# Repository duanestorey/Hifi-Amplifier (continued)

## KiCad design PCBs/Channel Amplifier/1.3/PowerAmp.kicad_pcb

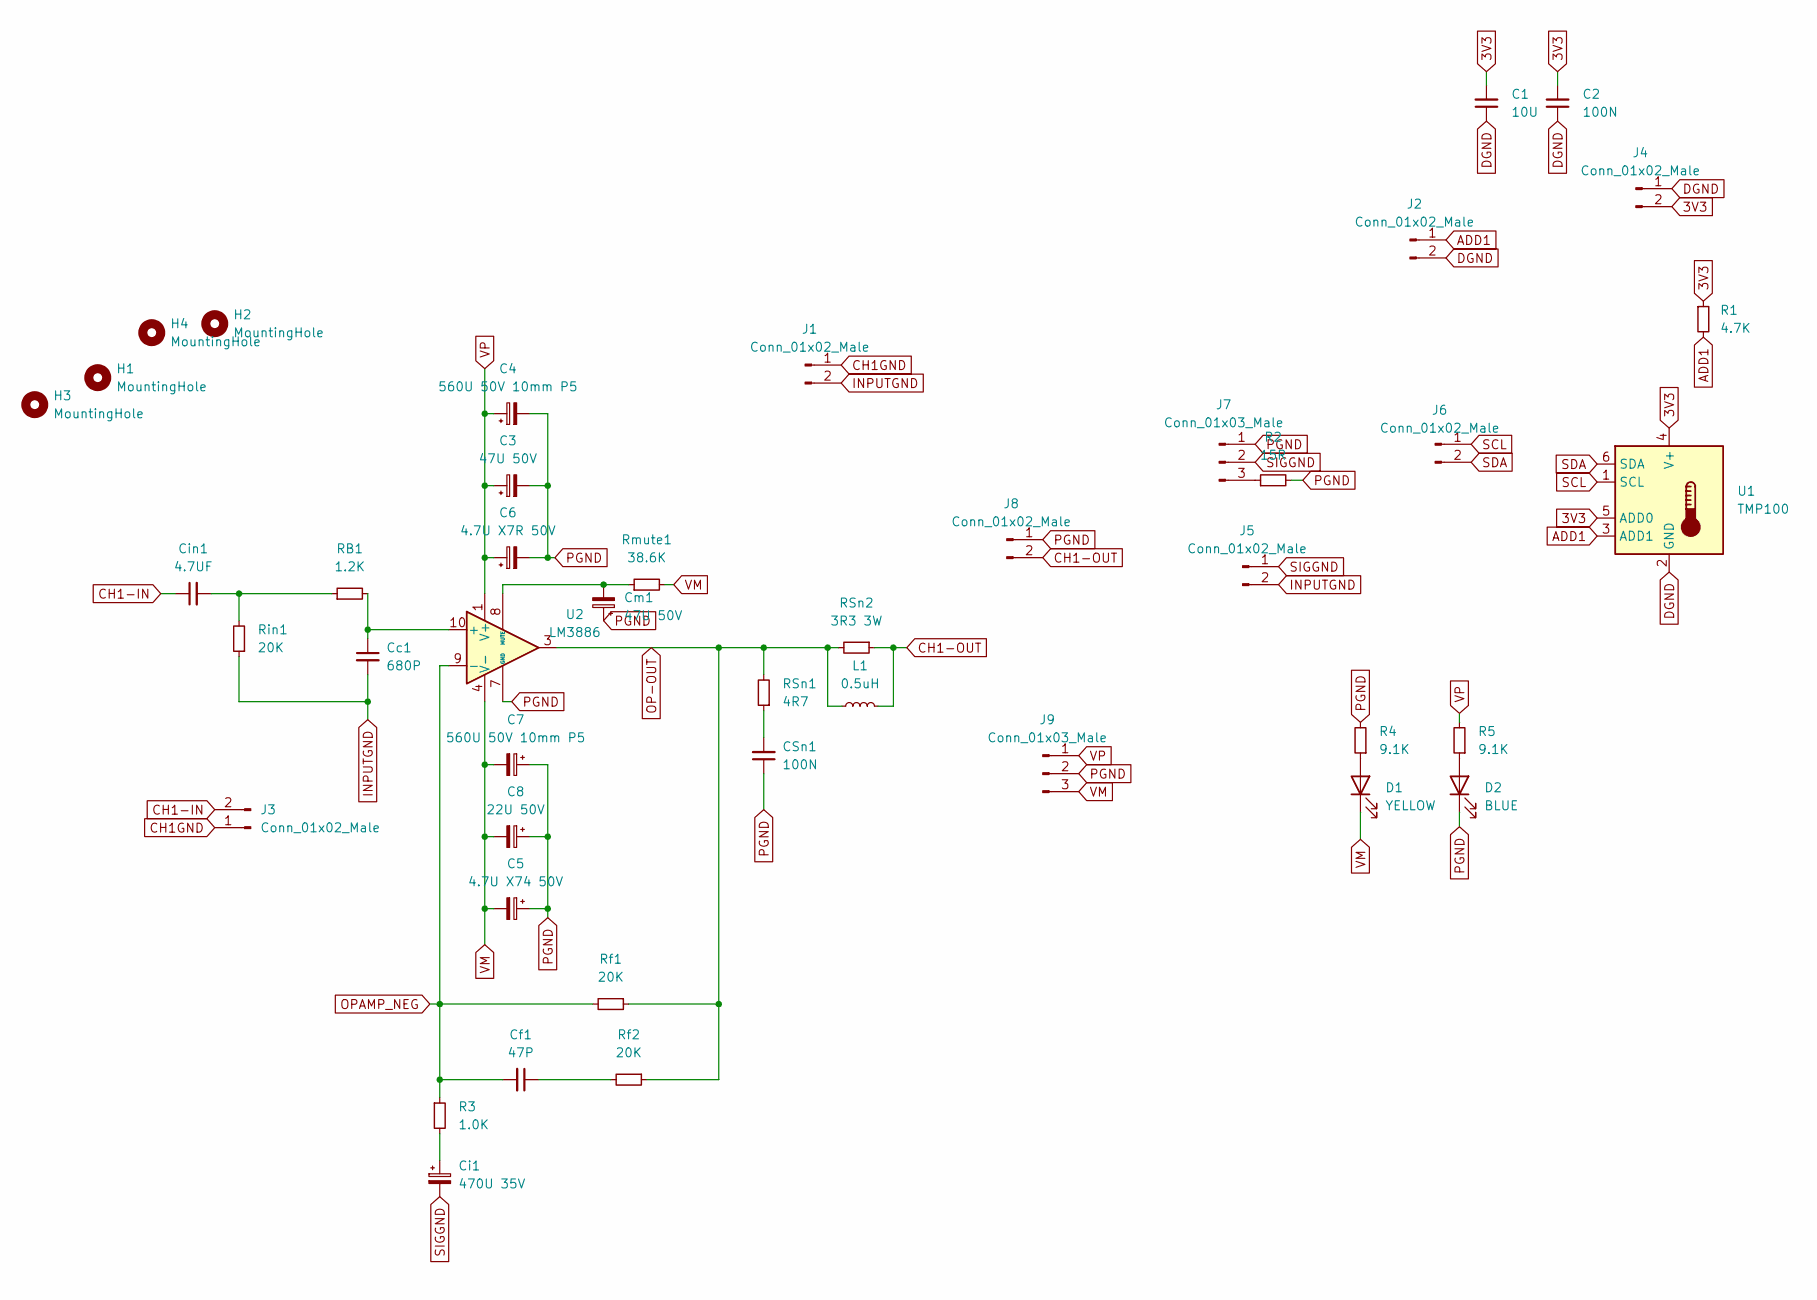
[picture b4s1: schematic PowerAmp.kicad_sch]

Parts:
C1: 10U; R_1206_3216Metric_Pad1.30x1.75mm_HandSolder
C2: 100N; R_0805_2012Metric_Pad1.20x1.40mm_HandSolder
C3: 47U 50V; CP_Radial_D6.3mm_P2.50mm
C4, C7: 560U 50V 10mm P5; CP_Radial_D12.5mm_P5.00mm
C5: 4.7U X74 50V; C_Disc_D6.0mm_W4.4mm_P5.00mm
C6: 4.7U X7R 50V; C_Disc_D6.0mm_W4.4mm_P5.00mm
C8: 22U 50V; CP_Radial_D6.3mm_P2.50mm
CSn1: 100N; C_Rect_L10.3mm_W4.5mm_P7.50mm_MKS4
Cc1: 680P; C_Disc_D11.0mm_W5.0mm_P10.00mm
Cf1: 47P; C_Disc_D9.0mm_W5.0mm_P7.50mm
Ci1: 470U 35V; CP_Radial_D10.0mm_P5.00mm
Cin1: 4.7UF; CP_Radial_D5.0mm_P2.00mm
Cm1: 47U 50V; CP_Radial_D6.3mm_P2.50mm
D1: YELLOW; LED_0805_2012Metric_Pad1.15x1.40mm_HandSolder
D2: BLUE; LED_0805_2012Metric_Pad1.15x1.40mm_HandSolder
H1, H2, H3, H4: MountingHole; MountingHole_3mm
J1, J2, J5: Conn_01x02_Male; PinHeader_1x02_P2.54mm_Vertical
J3, J4, J6: Conn_01x02_Male; JST_PH_B2B-PH-K_1x02_P2.00mm_Vertical
J7: Conn_01x03_Male; PinHeader_1x03_P2.54mm_Vertical
J8: Conn_01x02_Male; JST_VH_B2P-VH_1x02_P3.96mm_Vertical
J9: Conn_01x03_Male; JST_VH_B3P-VH-B_1x03_P3.96mm_Vertical
L1: 0.5uH; L_Radial_D12.0mm_P10.00mm_Neosid_SD12_style1
R1: 4.7K; R_0603_1608Metric_Pad0.98x0.95mm_HandSolder
R2: 15R; R_1206_3216Metric_Pad1.30x1.75mm_HandSolder
R3: 1.0K; R_Axial_DIN0207_L6.3mm_D2.5mm_P10.16mm_Horizontal
R4, R5: 9.1K; R_0805_2012Metric_Pad1.20x1.40mm_HandSolder
RB1: 1.2K; R_Axial_DIN0207_L6.3mm_D2.5mm_P10.16mm_Horizontal
RSn1: 4R7; R_Axial_DIN0411_L9.9mm_D3.6mm_P12.70mm_Horizontal
RSn2: 3R3 3W; R_Axial_DIN0516_L15.5mm_D5.0mm_P20.32mm_Horizontal
Rf1, Rf2: 20K; R_Axial_DIN0207_L6.3mm_D2.5mm_P10.16mm_Horizontal
Rin1: 20K; R_Axial_DIN0207_L6.3mm_D2.5mm_P10.16mm_Horizontal
Rmute1: 38.6K; R_Axial_DIN0207_L6.3mm_D2.5mm_P10.16mm_Horizontal
U1: TMP100; SOT-23-6
U2: LM3886; TO-220-11_P3.4x5.08mm_StaggerOdd_Lead4.85mm_Vertical

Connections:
3V3: C1.2, C2.2, J4.2, R1.1, U1.4 (V+), U1.5 (ADD0)
ADD1: J2.1, R1.2, U1.3 (ADD1)
CH1-IN: Cin1.1, J3.2
CH1-OUT: J8.2, L1.2, RSn2.1
CH1GND: J1.1, J3.1
DGND: C1.1, C2.1, J2.2, J4.1, U1.2 (GND)
INPUTGND: Cc1.2, J1.2, J5.2, Rin1.1
unnamed: CSn1.2, RSn1.1
unnamed: Cf1.1, Rf2.2
unnamed: Ci1.1, R3.2
unnamed: Cin1.2, RB1.1, Rin1.2
unnamed: D1.2 (A), R4.1
unnamed: D2.2 (A), R5.1
unnamed: J7.3, R2.1
unnamed: Cc1.1, RB1.2, U2.10 (+)
unnamed: Cm1.2, Rmute1.1, U2.8 (MUTE)
OP-OUT: L1.1, RSn1.2, RSn2.2, Rf1.1, Rf2.1, U2.3
OPAMP_NEG: Cf1.2, R3.1, Rf1.2, U2.9 (-)
PGND: C3.2, C4.2, C5.1, C6.2, C7.1, C8.1, CSn1.1, Cm1.1, D2.1 (K), J7.1, J8.1, J9.2, R2.2, R4.2, U2.7 (GND)
SCL: J6.1, U1.1 (SCL)
SDA: J6.2, U1.6 (SDA)
SIGGND: Ci1.2, J5.1, J7.2
VM: C5.2, C7.2, C8.2, D1.1 (K), J9.3, Rmute1.2, U2.4 (V-)
VP: C3.1, C4.1, C6.1, J9.1, R5.2, U2.1 (V+), U2.5 (V+)

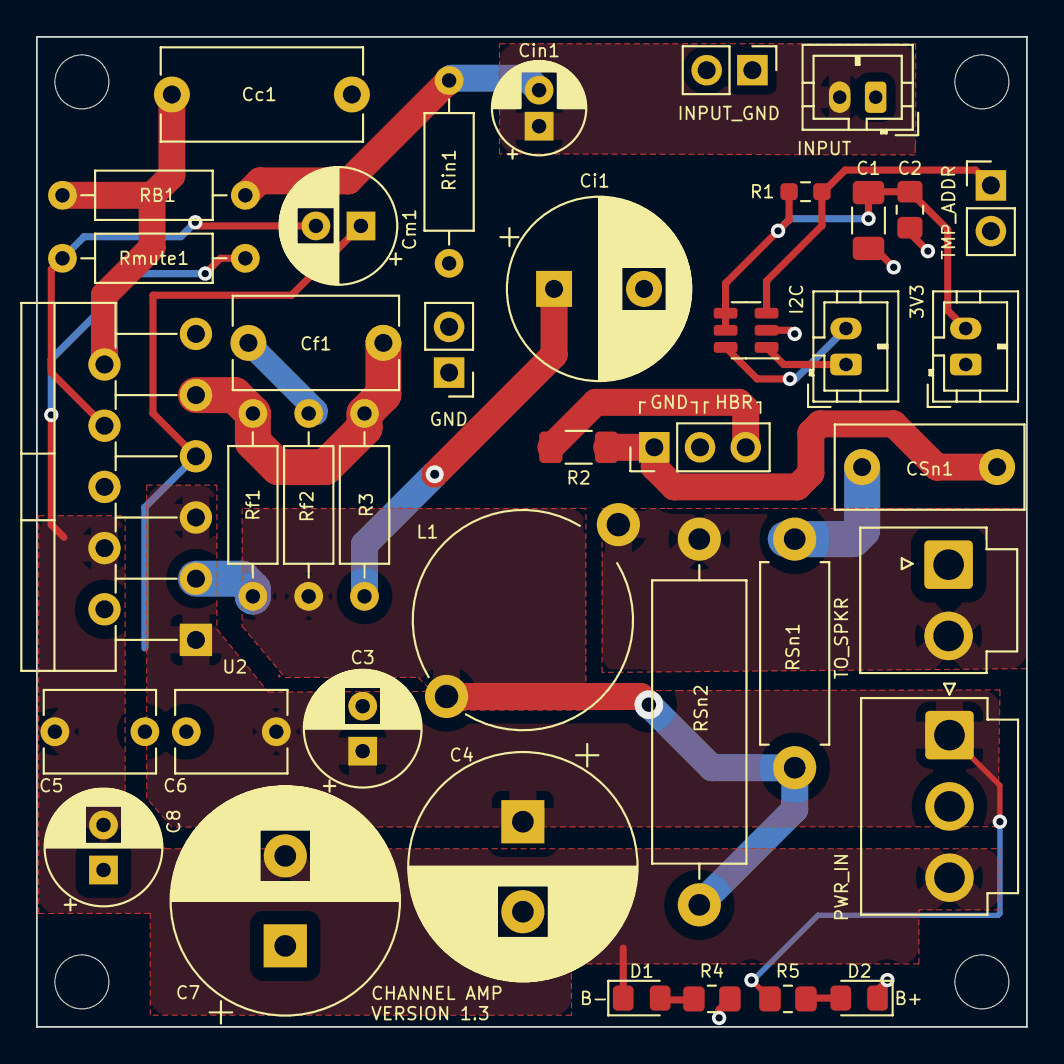
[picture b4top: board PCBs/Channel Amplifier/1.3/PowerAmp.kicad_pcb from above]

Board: 2 copper layers, 55.0 x 55.0 mm, 44 parts (0 on the bottom side), 24 nets.

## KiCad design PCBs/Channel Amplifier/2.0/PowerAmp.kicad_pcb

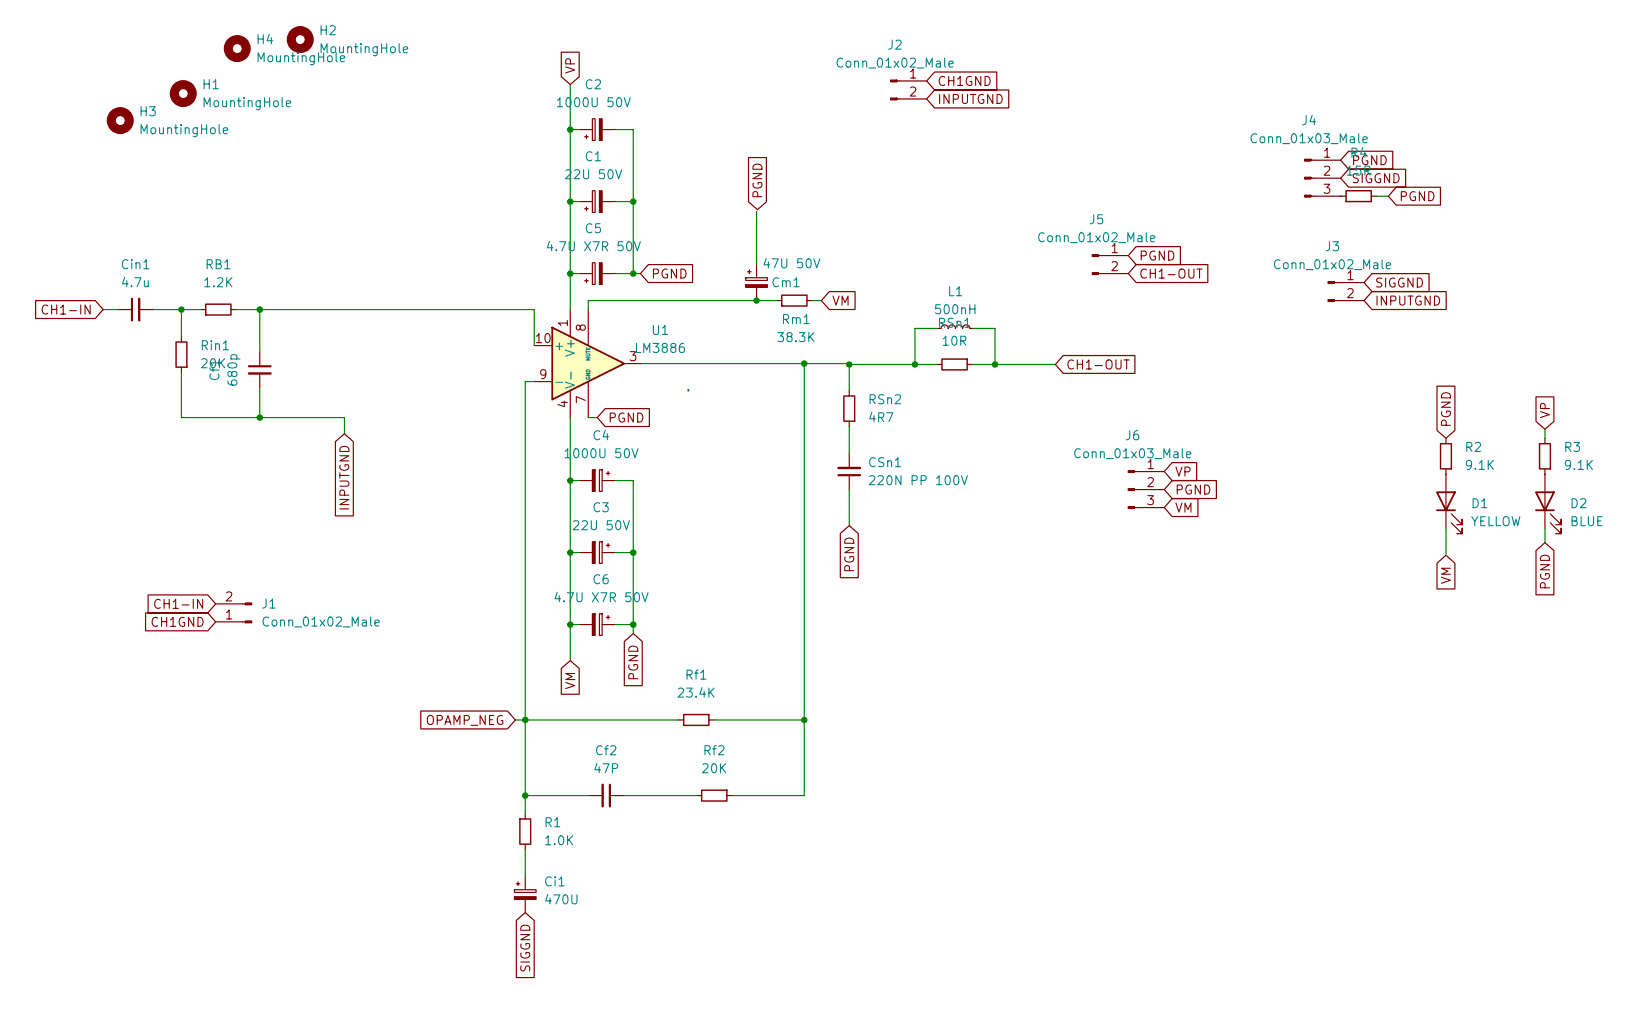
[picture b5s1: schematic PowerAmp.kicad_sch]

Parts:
C1, C3: 22U 50V; CP_Radial_D6.3mm_P2.50mm
C2, C4: 1000U 50V; CP_Radial_D12.5mm_P5.00mm
C5, C6: 4.7U X7R 50V; C_1206_3216Metric_Pad1.33x1.80mm_HandSolder
CSn1: 220N PP 100V; C_Rect_L18.0mm_W7.0mm_P15.00mm_FKS3_FKP3
Cf1: 680p; C_1206_3216Metric_Pad1.33x1.80mm_HandSolder
Cf2: 47P; C_1206_3216Metric_Pad1.33x1.80mm_HandSolder
Ci1: 470U; CP_Radial_D12.5mm_P5.00mm
Cin1: 4.7u; 4.7uF Polypropylene Aliexpress
Cm1: 47U 50V; CP_Radial_D6.3mm_P2.50mm
D1: YELLOW; LED_0805_2012Metric_Pad1.15x1.40mm_HandSolder
D2: BLUE; LED_0805_2012Metric_Pad1.15x1.40mm_HandSolder
H1, H2, H3, H4: MountingHole; MountingHole_3mm
J1: Conn_01x02_Male; JST_PH_B2B-PH-K_1x02_P2.00mm_Vertical
J2, J3: Conn_01x02_Male; PinHeader_1x02_P2.54mm_Vertical
J4: Conn_01x03_Male; PinHeader_1x03_P2.54mm_Vertical
J5: Conn_01x02_Male; JST_VH_B2P-VH_1x02_P3.96mm_Vertical
J6: Conn_01x03_Male; JST_VH_B3P-VH-B_1x03_P3.96mm_Vertical
L1: 500nH; 500nH Inductor Aliexpress Air Gap
R1: 1.0K; R_1206_3216Metric_Pad1.30x1.75mm_HandSolder
R2, R3: 9.1K; R_0805_2012Metric_Pad1.20x1.40mm_HandSolder
R4: 15R; R_0805_2012Metric_Pad1.20x1.40mm_HandSolder
RB1: 1.2K; R_1206_3216Metric_Pad1.30x1.75mm_HandSolder
RSn1: 10R; R_4020_10251Metric_Pad1.65x5.30mm_HandSolder
RSn2: 4R7; R_Axial_DIN0411_L9.9mm_D3.6mm_P12.70mm_Horizontal
Rf1: 23.4K; R_1206_3216Metric_Pad1.30x1.75mm_HandSolder
Rf2: 20K; R_1206_3216Metric_Pad1.30x1.75mm_HandSolder
Rin1: 20K; R_1206_3216Metric_Pad1.30x1.75mm_HandSolder
Rm1: 38.3K; R_1206_3216Metric_Pad1.30x1.75mm_HandSolder
U1: LM3886; TO-220-11_P3.4x5.08mm_StaggerOdd_Lead4.85mm_Vertical

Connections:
CH1-IN: Cin1.1, J1.2
CH1-OUT: J5.2, L1.2, RSn1.1
CH1GND: J1.1, J2.1
INPUTGND: Cf1.2, J2.2, J3.2, Rin1.1
unnamed: CSn1.2, RSn2.1
unnamed: Cf2.1, Rf2.2
unnamed: Ci1.1, R1.2
unnamed: Cin1.2, RB1.1, Rin1.2
unnamed: D1.2 (A), R2.1
unnamed: D2.2 (A), R3.1
unnamed: J4.3, R4.1
unnamed: L1.1, RSn1.2, RSn2.2, Rf1.1, Rf2.1, U1.3
unnamed: Cf1.1, RB1.2, U1.10 (+)
unnamed: Cm1.2, Rm1.1, U1.8 (MUTE)
OPAMP_NEG: Cf2.2, R1.1, Rf1.2, U1.9 (-)
PGND: C1.2, C2.2, C3.1, C4.1, C5.2, C6.1, CSn1.1, D2.1 (K), J4.1, J5.1, J6.2, R2.2, R4.2, U1.7 (GND)
SIGGND: Ci1.2, J3.1, J4.2
VM: C3.2, C4.2, C6.2, D1.1 (K), J6.3, Rm1.2, U1.4 (V-)
VP: C1.1, C2.1, C5.1, J6.1, R3.2, U1.1 (V+), U1.5 (V+)

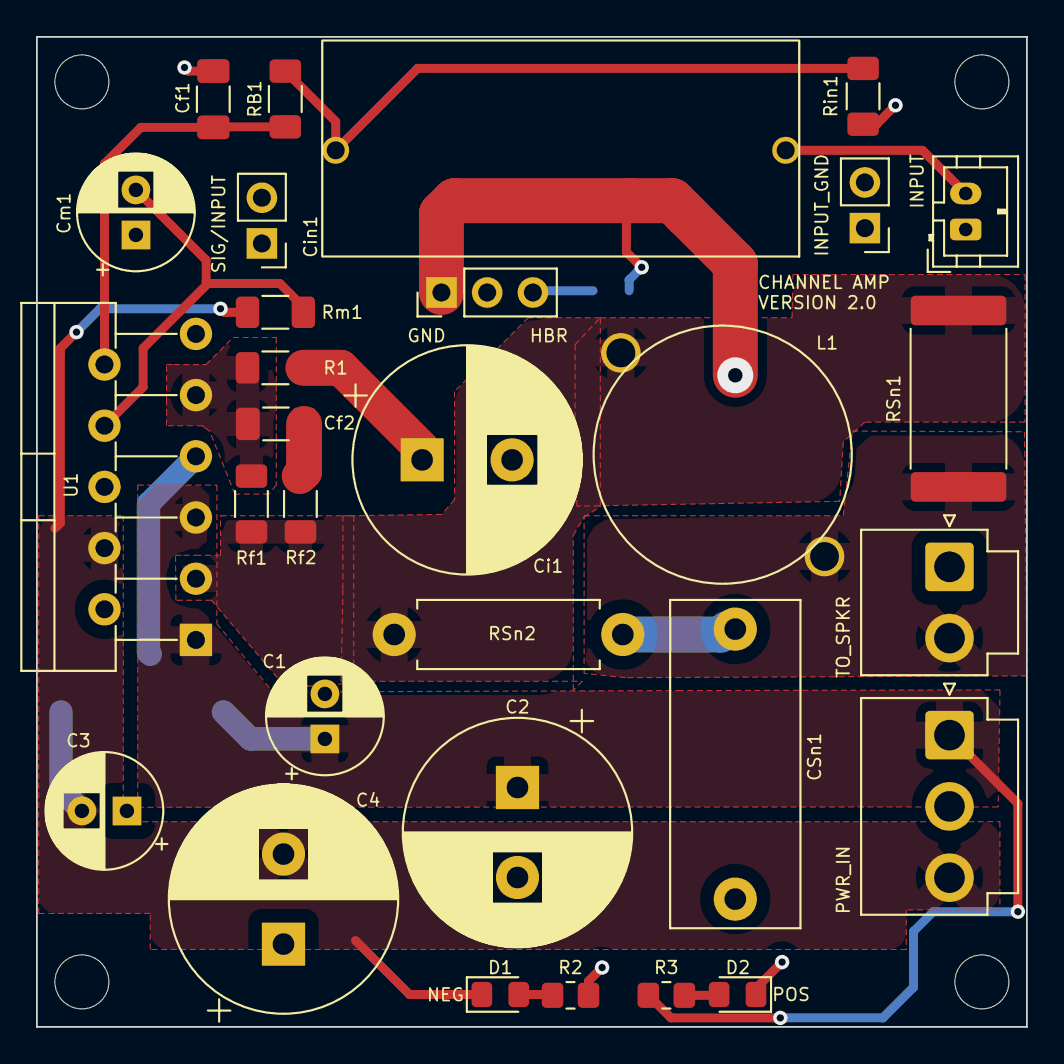
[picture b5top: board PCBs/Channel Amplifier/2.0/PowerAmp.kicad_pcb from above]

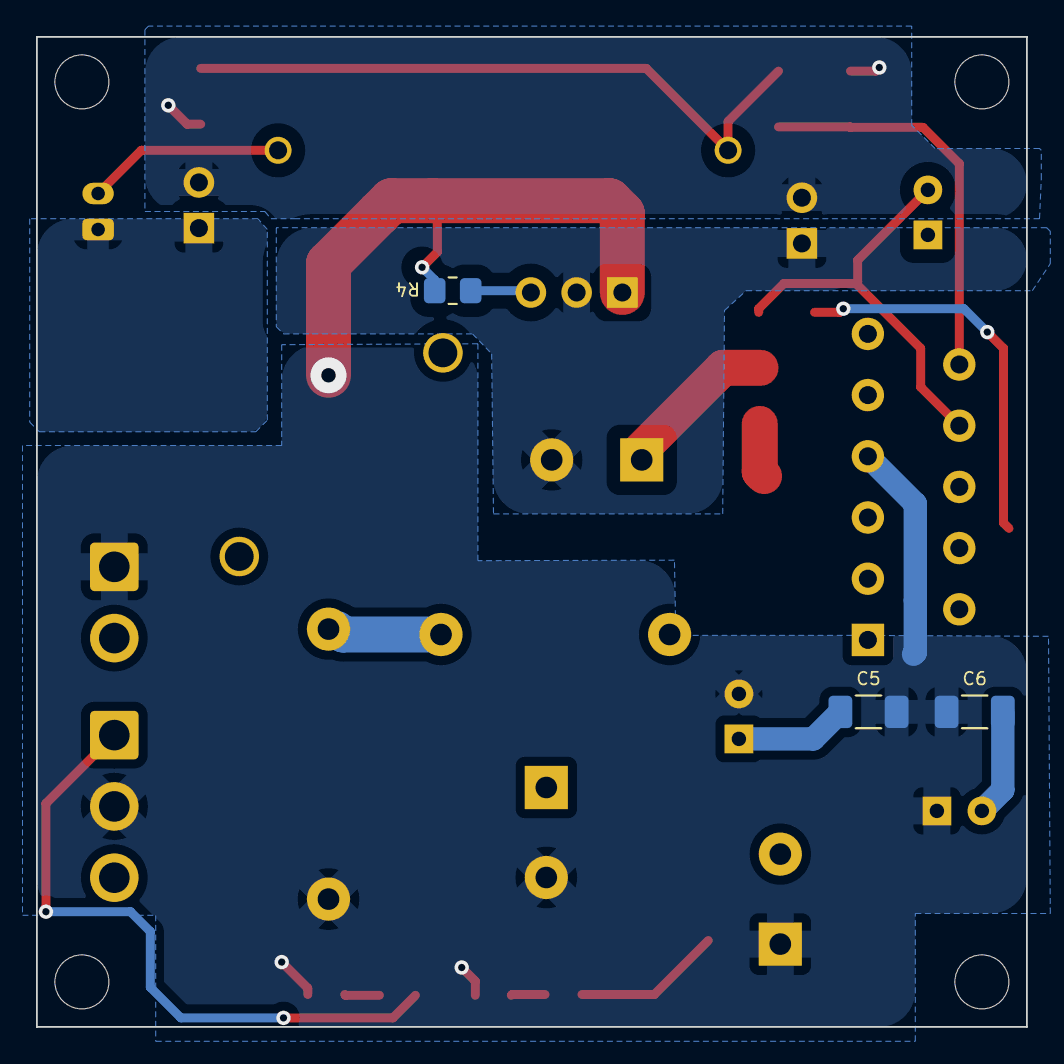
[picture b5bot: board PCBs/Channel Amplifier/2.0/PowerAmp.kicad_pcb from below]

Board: 2 copper layers, 55.0 x 55.0 mm, 37 parts (3 on the bottom side), 19 nets.

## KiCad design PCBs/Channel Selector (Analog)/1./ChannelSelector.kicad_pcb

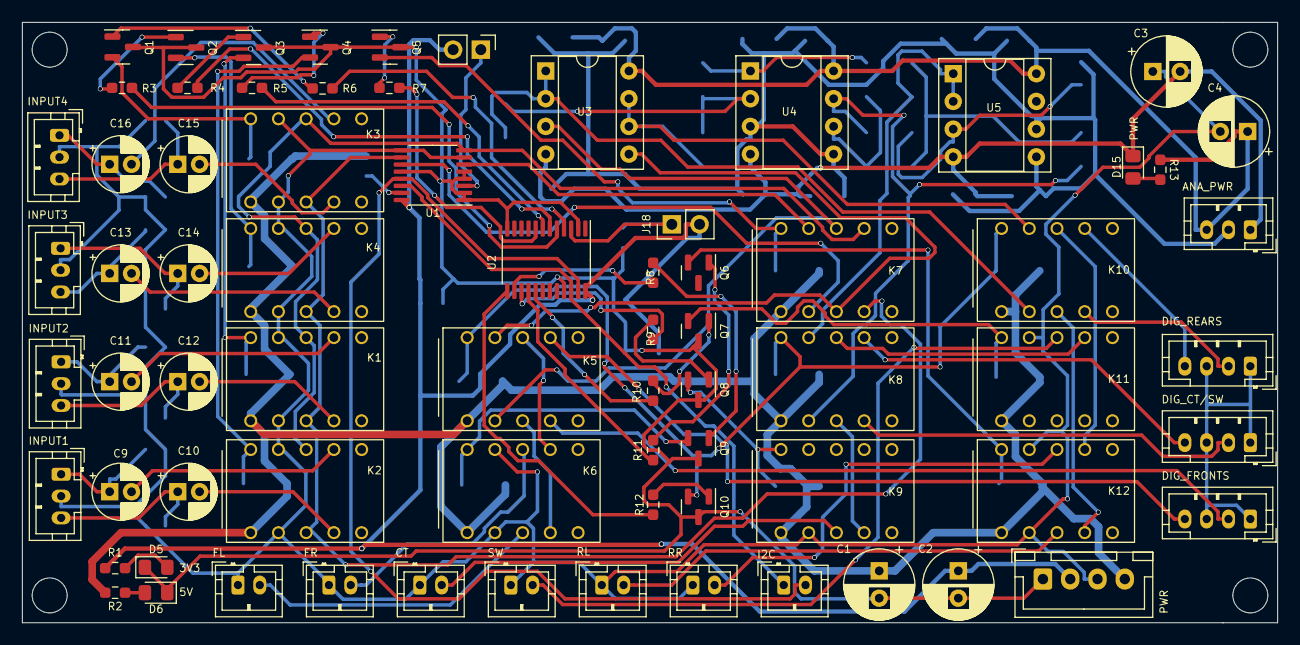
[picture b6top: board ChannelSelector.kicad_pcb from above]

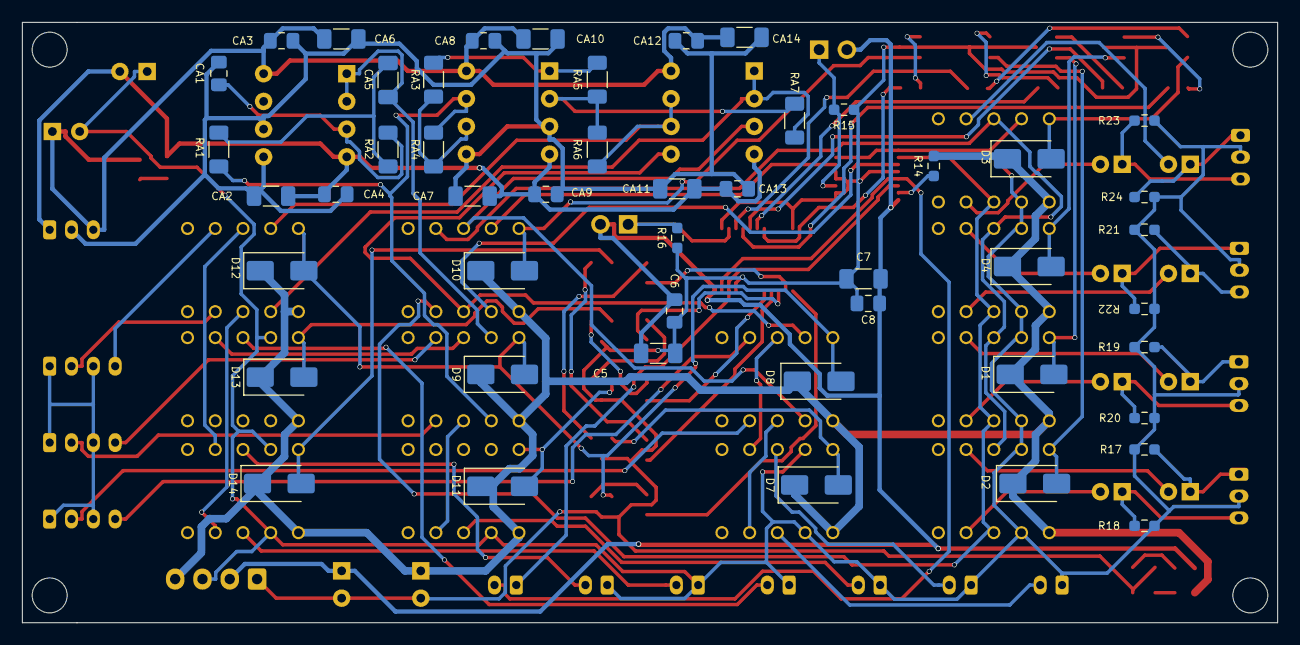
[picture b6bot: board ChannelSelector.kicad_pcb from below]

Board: 2 copper layers, 115.0 x 55.0 mm, 125 parts (48 on the bottom side), 95 nets.

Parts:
C1, C2, C3, C4: 100u; CP_Radial_D6.3mm_P2.50mm
C5, C7: 10U; C_1206_3216Metric_Pad1.33x1.80mm_HandSolder
C6, C8: 0.1U; C_0805_2012Metric_Pad1.18x1.45mm_HandSolder
C9, C10, C11, C12, C13, C14, C15, C16: 10u; CP_Radial_D5.0mm_P2.00mm
CA1: 10n; C_0805_2012Metric_Pad1.18x1.45mm_HandSolder
CA2, CA6, CA7, CA10, CA11, CA14: 10u; C_1206_3216Metric_Pad1.33x1.80mm_HandSolder
CA3, CA4, CA8, CA9, CA12, CA13: 0.1u; C_0805_2012Metric_Pad1.18x1.45mm_HandSolder
CA5: 100n; C_1206_3216Metric_Pad1.33x1.80mm_HandSolder
D1, D2, D3, D4, D7, D8, D9, D10, D11, D12, D13, D14: 1N4001; D_SMA
D5: YELLOW; LED_0805_2012Metric_Pad1.15x1.40mm_HandSolder
D6: BLUE; LED_0805_2012Metric_Pad1.15x1.40mm_HandSolder
D15: WHITE; LED_0805_2012Metric_Pad1.15x1.40mm_HandSolder
H1, H2, H3, H4: MountingHole; MountingHole_3.2mm_M3
J1, J2, J3, J4, J16: Conn_01x03_Pin; JST_PH_B3B-PH-K_1x03_P2.00mm_Vertical
J5, J6, J7, J8, J9, J10: Conn_01x02_Pin; JST_PH_B2B-PH-K_1x02_P2.00mm_Vertical
J11: Conn_01x02_Male; JST_PH_B2B-PH-K_1x02_P2.00mm_Vertical
J12: Conn_01x04_Pin; JST_XH_B4B-XH-A_1x04_P2.50mm_Vertical
J13, J14, J15: Conn_01x04_Pin; JST_PH_B4B-PH-K_1x04_P2.00mm_Vertical
J17, J18: Conn_01x02_Pin; PinHeader_1x02_P2.54mm_Vertical
K1, K3, K4, K5, K6, K7, K8, K9, K10, K11, K12: EC2-5NU; KEMET EA2
K2: KEMET; KEMET EA2
Q1, Q2, Q3, Q4, Q5, Q6, Q7, Q8, Q9, Q10: BC859; SOT-23
R1: 430R; R_0603_1608Metric_Pad0.98x0.95mm_HandSolder
R2, R15, R16: 670R; R_0603_1608Metric_Pad0.98x0.95mm_HandSolder
R3, R4, R5, R6, R7, R8, R9, R10, R11, R12: 1K; R_0603_1608Metric_Pad0.98x0.95mm_HandSolder
R13: 5K; R_0603_1608Metric_Pad0.98x0.95mm_HandSolder
R14: 0R; R_0603_1608Metric_Pad0.98x0.95mm_HandSolder
R17, R18, R19, R20, R21, R22, R23, R24: 10K; R_0603_1608Metric_Pad0.98x0.95mm_HandSolder
RA1: 7.5K; R_1206_3216Metric_Pad1.30x1.75mm_HandSolder
RA2: 130K; R_1206_3216Metric_Pad1.30x1.75mm_HandSolder
RA3, RA4, RA5: 1K; R_1206_3216Metric_Pad1.30x1.75mm_HandSolder
RA6, RA7: 2K; R_1206_3216Metric_Pad1.30x1.75mm_HandSolder
U1: DS1881; TSSOP-16_4.4x5mm_P0.65mm
U2: TCA9555; TSSOP-24_4.4x7.8mm_P0.65mm
U3, U4, U5: OPA2134; DIP-8_W7.62mm_Socket

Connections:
3V3: C2.1, C5.1, C6.1, C7.1, C8.1, J12.2, J17.2, J18.2, R1.1, U1.16 (VDD), U2.24 (VDD)
5CHGND: J13.1, J13.3, J14.1, J14.3, J15.1, J15.3
5V: C1.1, D1.1 (K), D2.1 (K), D3.1 (K), D4.1 (K), D7.1 (K), D8.1 (K), D9.1 (K), D10.1 (K), D11.1 (K), D12.1 (K), D13.1 (K), D14.1 (K), J12.4, K1.1, K2.1, K3.1, K4.1, K5.1, K6.1, K7.1, K8.1, K9.1, K10.1, K11.1, K12.1, R2.1, R14.2
AGND: C3.1, C4.2, J1.2, J2.2, J3.2, J4.2, J5.1, J6.1, J7.1, J8.1, J9.1, J10.1, J12.3, K1.3, K1.10, K2.3, K2.10, K3.3, K3.10, K4.3, K4.10, K6.3, K6.10, K9.3, K11.10, K12.3, K12.10, R17.1, R18.1, R19.1, R20.1, R21.1, R22.1, R23.1, R24.1, U1.7 (L0), U1.9 (L1)
CT: J7.2, K9.4
CT_A: K8.3, RA1.1, RA4.1, U4.7 (OutB)
CT_DIG: J14.2, K8.5
CT_EN: R9.1, U2.15 (IO1_2)
CT_SIG: K8.4, K9.5
DIGCTL: R12.1, U2.13 (IO1_0)
FL: J5.2, K6.4
FL_A: K5.3, K7.9, U3.3 (InA+)
FL_AIN: K1.9, K2.9, K3.9, K4.9, K7.8, U1.8 (H0)
FL_AV: K7.10, U1.6 (W0)
FL_DIG: J15.2, K5.5
FL_SIG: K5.4, K6.5
FR: J6.2, K6.9
FRONT_EN: R8.1, U2.14 (IO1_1)
FR_A: K5.10, K7.4, U3.5 (InB+)
FR_AIN: K1.4, K2.4, K3.4, K4.4, K7.5, U1.10 (H1)
FR_AV: K7.3, U1.11 (W1)
FR_DIG: J15.4, K5.8
FR_SIG: K5.9, K6.8
GND: C1.2, C2.2, C5.2, C6.2, C7.2, C8.2, D5.1 (K), D6.1 (K), J12.1, Q1.3 (C), Q2.3 (C), Q3.3 (C), Q4.3 (C), Q5.3 (C), Q7.3 (C), Q8.3 (C), Q9.3 (C), Q10.3 (C), R15.1, R16.1, U1.1 (GND), U1.2 (A2), U1.4 (V-), U1.5 (A0), U1.12 (~CE), U2.2 (A1), U2.12 (VSS), U2.21 (A0)
GPIO_A2: J18.1, R16.2, U2.3 (A2)
unnamed: CA5.2, RA1.2, RA2.1
unnamed: D1.2 (A), K1.12, Q3.2 (E)
unnamed: D2.2 (A), K2.12, Q4.2 (E)
unnamed: D3.2 (A), K3.12, Q1.2 (E)
unnamed: D4.2 (A), K4.12, Q2.2 (E)
unnamed: D5.2 (A), R1.2
unnamed: D6.2 (A), R2.2
unnamed: D7.2 (A), K6.12, Q9.2 (E)
unnamed: D10.2 (A), K7.12, Q5.2 (E)
unnamed: D11.2 (A), K9.12, Q8.2 (E)
unnamed: D8.2 (A), D9.2 (A), D12.2 (A), K5.12, K8.12, K10.12, Q10.2 (E)
unnamed: D13.2 (A), K11.12, Q7.2 (E)
unnamed: D14.2 (A), K12.12, Q6.2 (E)
unnamed: D15.2 (A), R13.2
unnamed: C16.1, J1.1, R24.2
unnamed: C15.1, J1.3, R23.2
unnamed: C14.1, J2.1, R22.2
unnamed: C13.1, J2.3, R21.2
unnamed: C11.1, J3.1, R19.2
unnamed: C12.1, J3.3, R20.2
unnamed: C9.1, J4.1, R17.2
unnamed: C10.1, J4.3, R18.2
unnamed: Q1.1 (B), R6.2
unnamed: Q2.1 (B), R3.2
unnamed: Q3.1 (B), R4.2
unnamed: Q4.1 (B), R5.2
unnamed: Q5.1 (B), R7.2
unnamed: Q6.1 (B), R11.2
unnamed: Q7.1 (B), R10.2
unnamed: Q8.1 (B), R9.2
unnamed: Q9.1 (B), R8.2
unnamed: Q10.1 (B), R12.2
unnamed: R14.1, U1.15 (VCC)
unnamed: RA5.1, RA6.2, RA7.2, U4.2 (InA-)
unnamed: RA3.1, RA4.2, U4.6 (InB-)
unnamed: RA3.2, RA5.2, U4.1 (OutA)
unnamed: CA1.2, RA2.2, U5.3 (InA+)
OPGND: CA1.1, CA2.1, CA3.1, CA4.1, CA6.1, CA7.1, CA8.1, CA9.1, CA10.1, CA11.1, CA12.1, CA13.1, CA14.1, J16.2, U4.3 (InA+), U4.5 (InB+), U5.5 (InB+), U5.6 (InB-)
POT_A1: J17.1, R15.2, U1.3 (A1)
RCA1: R5.1, U2.7 (IO0_3)
RCA1_L: C9.2, K2.8
RCA1_R: C10.2, K2.5
RCA2: R4.1, U2.6 (IO0_2)
RCA2_L: C11.2, K1.8
RCA2_R: C12.2, K1.5
RCA3: R3.1, U2.5 (IO0_1)
RCA3_L: C14.2, K4.8
RCA3_R: C13.2, K4.5
RCA4: R6.1, U2.4 (IO0_0)
RCA4_L: C16.2, K3.8
RCA4_R: C15.2, K3.5
REARS_EN: R11.1, U2.16 (IO1_3)
RL: J9.2, K12.4
RL_A: K10.3, RA7.1, U3.1 (OutA), U3.2 (InA-)
RL_DIG: J13.2, K10.5
RL_SIG: K10.4, K12.5
RR: J10.2, K12.9
RR_A: K10.10, RA6.1, U3.6 (InB-), U3.7 (OutB)
RR_DIG: J13.4, K10.8
RR_SIG: K10.9, K12.8
SCL: J11.1, U1.14 (SCL), U2.22 (SCL)
SDA: J11.2, U1.13 (SDA), U2.23 (SDA)
SW: J8.2, K11.9
SW_A: CA5.1, K8.10, U5.1 (OutA), U5.2 (InA-)
SW_DIG: J14.4, K8.8
SW_EN: R10.1, U2.17 (IO1_4)
SW_SIG: K8.9, K11.8
V+: C4.1, CA3.2, CA6.2, CA8.2, CA10.2, CA12.2, CA14.2, J16.3, R13.1, U3.8 (V+), U4.8 (V+), U5.8 (V+)
V-: C3.2, CA2.2, CA4.2, CA7.2, CA9.2, CA11.2, CA13.2, D15.1 (K), J16.1, U3.4 (V-), U4.4 (V-), U5.4 (V-)
VOLCTL: R7.1, U2.8 (IO0_4)
